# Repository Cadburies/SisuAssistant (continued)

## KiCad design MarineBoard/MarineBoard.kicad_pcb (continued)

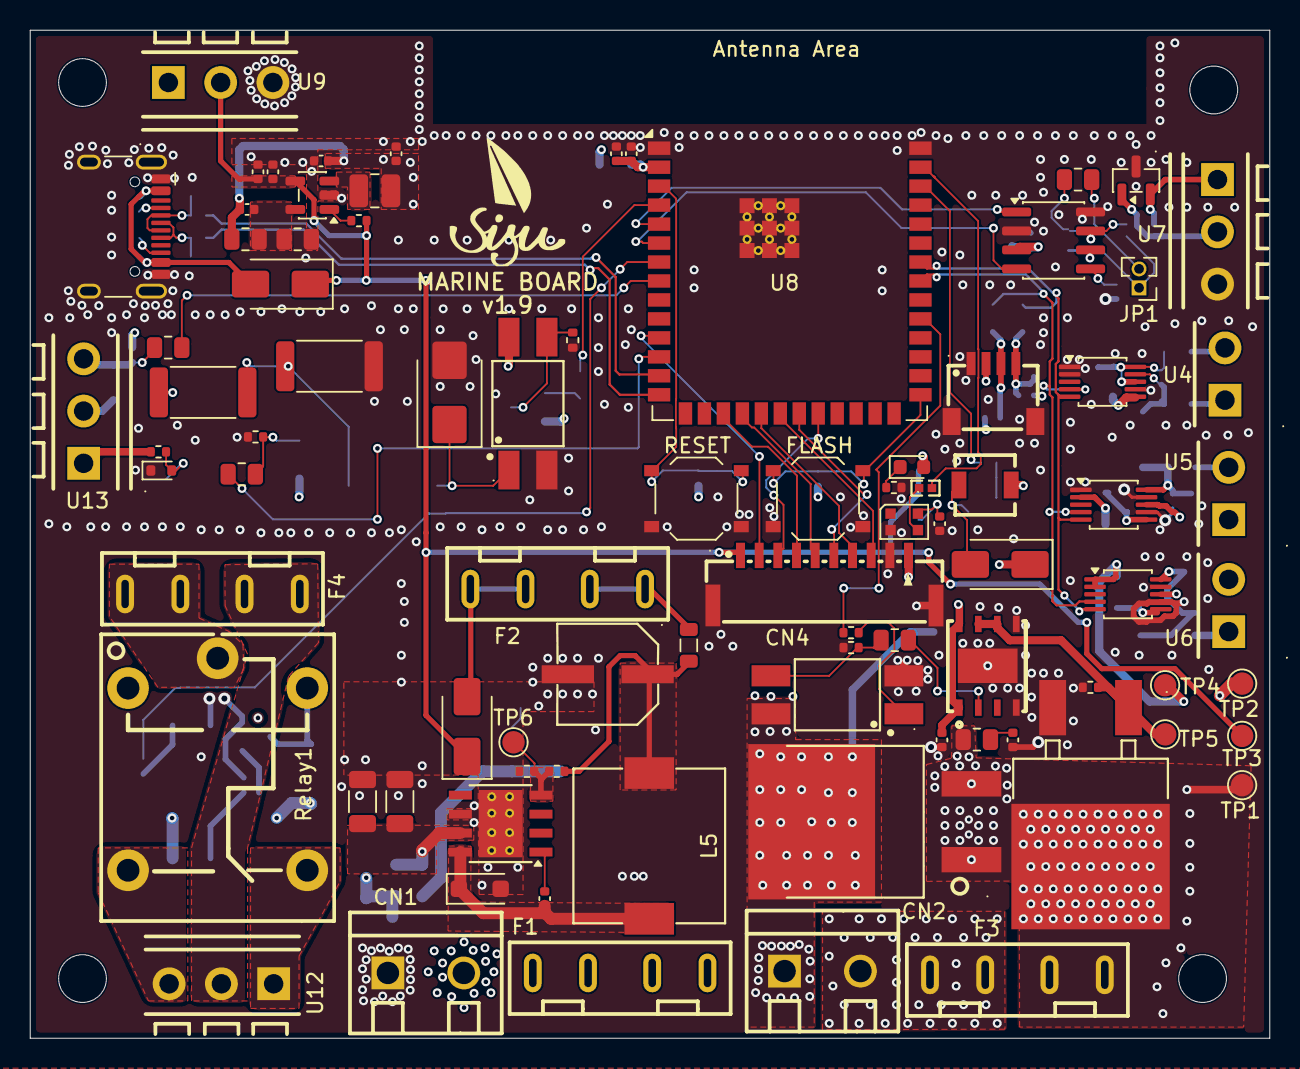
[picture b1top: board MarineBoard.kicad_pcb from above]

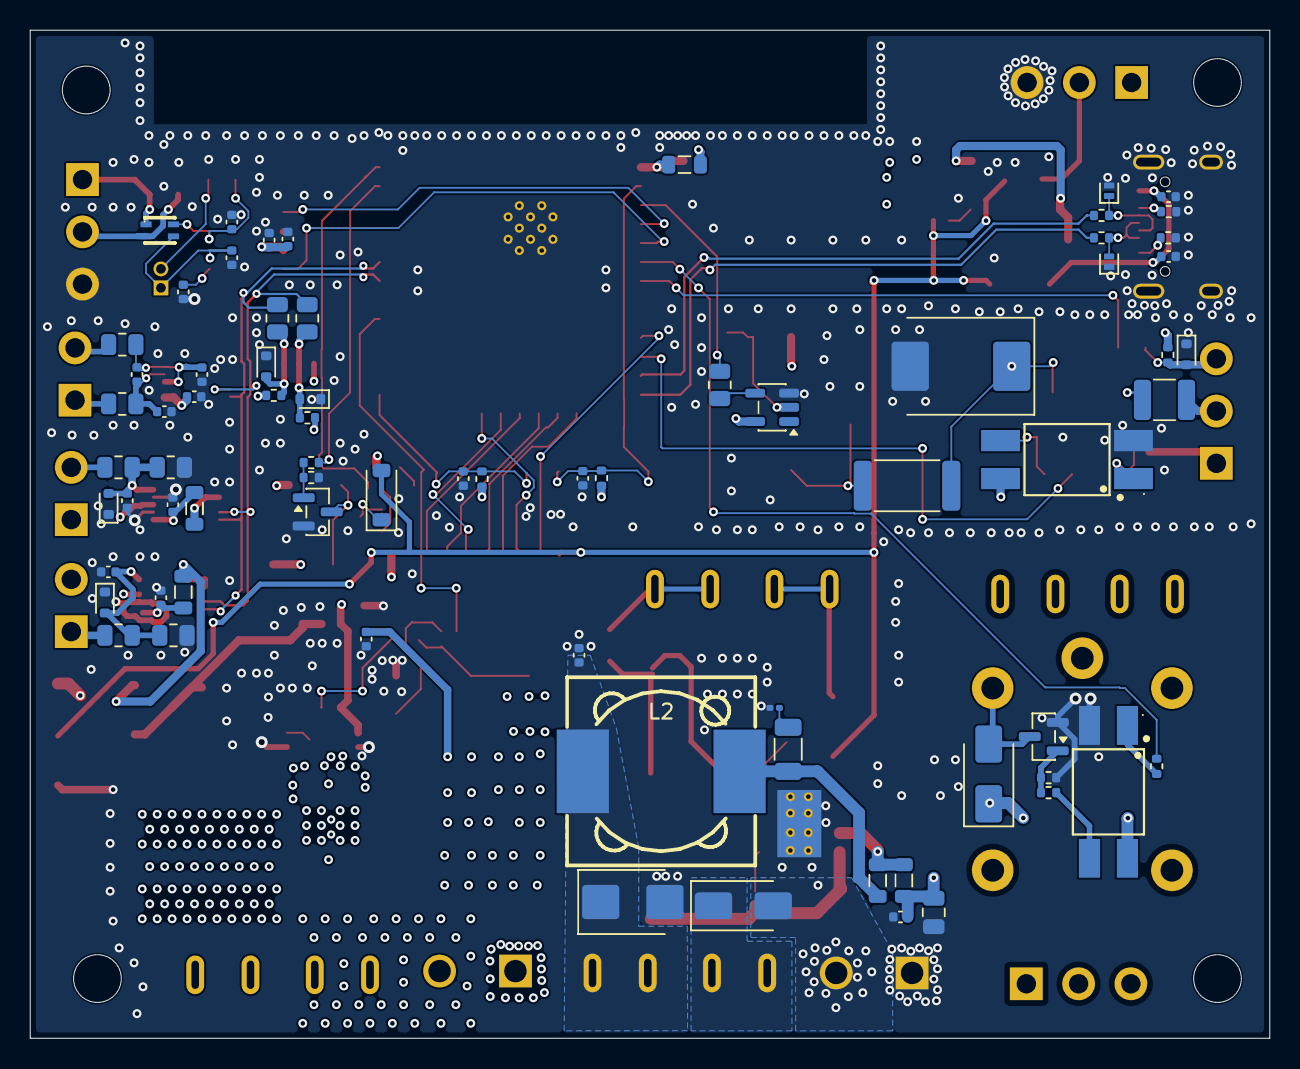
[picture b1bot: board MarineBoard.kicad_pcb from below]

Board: 4 copper layers, 83.0 x 67.5 mm, 162 parts (72 on the bottom side), 95 nets.

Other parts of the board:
LOGO1: v1.9; Sisu_Logo

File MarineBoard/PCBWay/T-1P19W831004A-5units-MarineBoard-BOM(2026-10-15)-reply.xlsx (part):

PCBWay Bom Quotation, Product No.:T-1P19W831004A
Item # | *Designator | *Qty | Manufacturer | *Mfg Part # | Description / Value | *Package/Footprint | Mounting Type | Your Instructions / Notes | Assembly requirement | *Unit Price(5 units) | *Total | *Delivery Time | *Actual Purchase Mfg Part # | *PCBWay Note | Customer Reply | PCBWay Update
1 | BUZZER1 | 1 | KELIKING | KLJ-4020 | 2V~4V 100mA 4kHz 73dB SMD,4x4mm『 』KLJ-4020 | BUZ-SMD_L4.0-W4.0-P3.50-L | SMD |  | Top | 2.174 | 10.87
2 | C1,C25 | 2 | Samsung Electro-Mechanics | CL05A106MQ5NUNC | 10uF ±20% 6.3V Ceramic Capacitor X5R 0402『 』10uF | C_0402_1005Metric | SMD |  | Bottom/Top | 0.099 | 0.99
3 | C2,C3,C5,C7,C9,C24,C27,C28,C31,C32,C34,C35,C36,C37,C38,C40 | 16 | Samsung Electro-Mechanics | CL05B104KO5NNNC | 100nF +/-10% 16V Ceramic Capacitor X7R 0402『 』0.1uF | C_0402_1005Metric | SMD |  | Bottom/Top | 0.008999999999999999 | 0.72
4 | C4,C8 | 2 | muRata | GRM158R61A226ME15D | 22uF +/-20% 10V Ceramic Capacitor X5R 0402『 』22uF | C_0402_1005Metric | SMD |  | Top | 1.029 | 10.29
5 | C6 | 1 | muRata | GJM1555C1H6R8BB01D | 6.8pF 50V Ceramic Capacitor C0G 0402『 』6.8pF | C_0402_1005Metric | SMD |  | Top | 0.266 | 1.33
6 | C11,C12,C14,C19,C42 | 5 | Samsung Electro-Mechanics | CL05B104KB5NNNC | 100nF ±10% 50V Ceramic Capacitor X7R 0402『 』0.1uF | C_0402_1005Metric | SMD |  | Bottom | 0.026 | 0.65
7 | C13 | 1 | muRata | GRM21BR61H106KE43L | 10uF ±10% 50V Ceramic Capacitor X5R 0805『 』10uF/50V | C_0805_2012Metric | SMD |  | Bottom | 0.8 | 4
8 | C15 | 1 | muRata | GRM31CR61E476ME44L | 47uF ±20% 25V Ceramic Capacitor X5R 1206『 』47uF | C_1206_3216Metric | SMD |  | Bottom | 1.959 | 9.795
9 | C16 | 1 | Samsung Electro-Mechanics | CL31B475KBHNNNE | 4.7uF +/-10% 50V Ceramic Capacitor X7R 1206『 』4.7uF | C_1206_3216Metric | SMD |  | Top | 0.485 | 2.425
10 | C17 | 1 | Samsung Electro-Mechanics | CL31A106KBHNNNE | 10uF +/-10% 50V Ceramic Capacitor X5R 1206『 』10uF | C_1206_3216Metric | SMD |  | Top | 1.029 | 5.145
11 | C18 | 1 | Samsung Electro-Mechanics | CL05B103KB5NNNC | 10nF ±10% 50V Ceramic Capacitor X7R 0402『 』10nF | C_0402_1005Metric | SMD |  | Top | 0.126 | 0.63
12 | C20 | 1 | Panasonic | 10SVPE220M | 220uF ±20% 10V OS-CON polymer, ESR 20mΩ, SMD D6.3xL5.9mm (TPS5430 internal comp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 | CAP-SMD_BD6.3-L6.6-W6.6-FD | SMD |  | Top | 3.893 | 19.465
13 | C26,C29 | 2 | muRata | GCM155R71H473KE02D | 47nF ±10% 50V Ceramic Capacitor X7R 0402『 』47nF | C_0402_1005Metric | SMD |  | Bottom | 0.064 | 0.64
14 | C30 | 1 | Samsung Electro-Mechanics | CL05A475MP5NRNC | 4.7uF ±20% 10V Ceramic Capacitor X5R 0402『 』4.7uF | C_0402_1005Metric | SMD |  | Bottom | 0.107 | 0.535
15 | C33 | 1 | muRata | GRM155R61H105KE05D | 1uF ±10% 50V Ceramic Capacitor X5R 0402『 』1uF | C_0402_1005Metric | SMD |  | Top | 0.219 | 1.095
16 | C39 | 1 | PSA | FS32X125K101EGG | 1.2uF +/-10% 100V Ceramic Capacitor X7R 1210『 』1.2uF 100V | C_1210_3225Metric | SMD |  | Bottom | 1.01 | 5.05
17 | CN1,CN2 | 2 | Phoenix Contact | 1729128 | 1.5 17.5A 400V 1x2P Green 16~26 Through Hole 2 1 5.08mm Through Hole,P=5.08mm W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 | CONN-TH_2P-P5.08_1729128 | THT |  | Top | 0.509 | 5.09
18 | CN3 | 1 | JST | SM04B-SRSS-TB(LF)(SN) | Connector Header 4 position 1mm Pitch 1A Surface Mount, Right Angle -25℃~+85℃『 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 | CONN-SMD_4P-P1.00_SM04B-SRSS-TB-LF-SN | SMD |  | Top | 0.712 | 3.56
19 | CN4 | 1 | JST | BM10B-GHS-TBT(LF)(SN) | BM10B-GHS-TBT | CONN-SMD_BM10B-GHS-TBT-LF-SN | SMD |  | Top | 1.57 | 7.850000000000001
20 | D1,D4,D15,D17 | 4 | onsemi | SS14 | 40V 1A Schottky diode, SMA (DO-214AC)『 』SS14 | D_SMA | SMD |  | Bottom/Top | 0.25 | 5
21 | D2,D3 | 2 | R+O | H5VL10B | 5V bidirectional ESD diode H5VL10B. Manufacturer package DFN1006-2L. Board land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 | DFN1006-2L | SMD |  | Bottom | 0.041 | 0.41 |  |  | The correct package for the listed Part Number [H5VL10B] is indeed [DFN1006-2L]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 | Yes. Fit H5VL10B. The manufacturer package is DFN1006-2L. D_SOD-882 is the same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
22 | D5 | 1 | Worldsemi | WS2812B-2020-V6 | RGB LED with integrated controller, Worldsemi WS2812B-2020-V6, 2.0 x 2.0 mm | LED_WS2812B-2020_PLCC4_2.0x2.0mm | SMD |  | Top | 0.062 | 0.31 |  | WS2812B-2020-V6 | The part we supply is WS2812B-2020-V6 OK? | Yes. Fit Worldsemi WS2812B-2020-V6.
23 | D6 | 1 | Littelfuse | SMBJ18A | 18V TVS diode, SMB (DO-214AA)『 』SMBJ18A | D_SMB | SMD |  | Bottom | 0.993 | 4.965 | 7-10 Workdays
24 | D7 | 1 | LRC | LMBR340FT1G | Schottky diode, SOD-123F『 』LMBR340FT1G | D_SOD-123F | SMD |  | Top | 0.169 | 0.8450000000000001
25 | D8 | 1 | Vishay | VS-43CTQ100S-M3 | Dual Schottky rectifier, D2PAK『 』VS-43CTQ100S-M3 | D2PAK_L10.0-W9.0-P2.54-LS15.0-TL-1 | SMD |  | Top | 3.623 | 18.115
26 | D9,D11,D12,D13,D18,D19 | 6 | onsemi | ESD5Z3.3T1G | 3.3V ESD protection diode, SOD-523『 』ESD5Z3.3T1G | D_SOD-523 | SMD |  | Bottom/Top | 0.114 | 3.42
27 | D10 | 1 | UMW | PESD1CAN | CAN bus ESD protection, SOT-23『 』PESD1CAN | SOT-23 | SMD |  | Top | 0.145 | 0.725
28 | D14 | 1 | R+O | SS56 | 60V 5A Schottky diode, SMA『 』SS56 | D_SMA | SMD |  | Bottom | 0.081 | 0.405
29 | D16 | 1 | KENTO | KT-0603R | Red LED 0603『 』KT-0603R | LED_0603_1608Metric | SMD |  | Top | 0.07199999999999999 | 0.36
30 | D20 | 1 | onsemi | MBRS3100T3G | Schottky rectifier, SMC『 』MBRS3100T3G | D_SMC | SMD |  | Bottom | 0.483 | 2.415
31 | D21 | 1 | Diodes Incorporated | 1N4148W-7-F | 75V 150mA switching diode, SOD-123, Diodes Inc 1N4148W-7-F | D_SOD-123 | SMD |  | Bottom | 0.338 | 1.69 | 7-10 Workdays |  | The quoted part number is [1N4148W-7-F], not [WS2812B] as specified in descript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 | Fit Diodes Inc 1N4148W-7-F. This position is a switching diode. The old descrip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
32 | D22 | 1 | Diodes Inc | S3MB-13-F | 1000V 3A rectifier, SMB『 』S3MB-13-F | D_SMB | SMD |  | Top | 0.483 | 2.415
33 | F1 | 1 | XFCN | XF-506P | XF-506P MINI blade fuse holder. Insert Eaton Bussmann ATM-2, 2 A 32 V MINI blad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 | FUSE-TH_XF-506P | THT | Insert Eaton Bussmann ATM-2 into this holder | Top | 0.192 | 0.96 |  |  |  | Solder this holder, then insert Eaton Bussmann ATM-2, 2 A 32 V MINI blade, into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
34 | F2 | 1 | XFCN | XF-506P | XF-506P MINI blade fuse holder. Insert Eaton Bussmann ATM-1, 1 A 32 V MINI blad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 | FUSE-TH_XF-506P | THT | Insert Eaton Bussmann ATM-1 into this holder | Top | 0.192 | 0.96 |  |  |  | Solder this holder, then insert Eaton Bussmann ATM-1, 1 A 32 V MINI blade, into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
35 | F3,F4 | 2 | XFCN | XF-506P | XF-506P MINI blade fuse holder. Insert Eaton Bussmann ATM-10, 10 A 32 V MINI bl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 | FUSE-TH_XF-506P | THT | Insert Eaton Bussmann ATM-10 into each holder | Top | 0.144 | 1.44 |  |  |  | Solder these holders, then insert one Eaton Bussmann ATM-10, 10 A 32 V MINI bla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
36 | Flash1 | 1 | XKB | TS-1187A-B-A-B | TS-1187A tactile switch, 2 pin『 』Flash | SW_Push_1P1T_XKB_TS-1187A | SMD |  | Top | 0.07199999999999999 | 0.36
37 | J1 | 1 | HCTL | HC-TYPE-C-16P-01A | USB 2.0-only 16P Type-C receptacle『 』USB_C_Receptacle_USB2.0_16P | USB_C_Receptacle_HCTL_HC-TYPE-C-16P-01A | SMD |  | Top | 0.242 | 1.21
38 | JP1 | 1 | BOOMELE | 1.27-1*2PPin | 1.27 mm 1x2 vertical pin header. Fit BOOMELE shunt MPN 1.27, LCSC C150949, onto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 | PinHeader_1x02_P1.27mm_Vertical | THT | Fit the BOOMELE 1.27 shunt, LCSC C150949, onto these pins | Top | 0.254 | 1.27 |  | 1.27-1*2P针 |  | Fit BOOMELE shunt MPN 1.27, LCSC C150949, onto these pins.
39 | L1 | 1 | muRata | DFE252012F-1R0M=P2 | 1uH 3.3A shielded inductor, 1008『 』1uH 3.3A 40mΩ | L_1008_2520Metric | SMD |  | Top | 0.242 | 1.21
40 | L2 | 1 | FANGCHENG | FC-DR1207-220MT | 22uH +/-20% shielded inductor, 12.5x12.5 mm, Irms 4A, DCR 40 mohm『 』22uH | IND-SMD_L12.5-W12.5_B82477P4XX | SMD |  | Bottom | 0.39 | 1.95 |  | SMDRI129-220MT
41 | L3,L4,L6 | 3 | muRata | BLM21PG121SN1D | 120 ohm at 100 MHz ferrite bead, 0805『 』BLM21PG121SN1D | L_0805_2012Metric | SMD |  | Bottom/Top | 0.107 | 1.605
42 | L5 | 1 | Sumida | CDRH104RNP-150NC | 15uH shielded inductor, 10.2 x 10.0 mm『 』CDRH104RNP-150NC | IND-SMD_L10.2-W10.0 | SMD |  | Top | 0.966 | 4.83
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
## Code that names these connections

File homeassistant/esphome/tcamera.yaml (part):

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# assumed. Checked this exact "T-Camera" repo/product name too
# (Xinyuan-LilyGO/T-Camera) since the owner found it and it looked
# board-matching at a glance -- it's the SAME older/wrong generation as
# the doc above (three independent tells: XCLK=GPIO4 not 38, OLED I2C on
# 21/22 not 7/6, and critically an IP5306 power chip in its source vs the
# AXP2101 actually on this board/visible in the owner's photo). Not used.
#
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    type: std::string
    restore_value: no

# bus_a (GPIO7/6, OLED+AXP2101) DISABLED 2026-08-12: live hardware fault --
# this exact bus reproducibly wedges with "SCL is held LOW on the bus" /
# ESP-IDF bus-recovery failing, triggering a task-watchdog crash-loop that
# tripped ESPHome's built-in safe_mode. Confirmed the hang happens even
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# bus_b dedicated to the camera's own SCCB (register) interface.
i2c:
  - id: bus_b
    sda: GPIO5
    scl: GPIO4
    scan: true

esp32_camera:
  name: "Dinghy Camera"
  external_clock:
    pin: GPIO38
    frequency: 20MHz
  i2c_id: bus_b
  data_pins: [GPIO14, GPIO47, GPIO48, GPIO21, GPIO13, GPIO11, GPIO10, GPIO9]
  vsync_pin: GPIO8
  href_pin: GPIO18
  pixel_clock_pin: GPIO12
  reset_pin: GPIO39
  # No PSRAM (WROOM-1) -- frame_buffer_location: DRAM is the documented
  # workaround (esphome/issues#6996); XGA is the tested-working ceiling,
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          request_headers:
            Content-Type: application/json

# I2S microphone (T-Camera S3 reference: WS=GPIO42, DATA=GPIO41,
# CLK=GPIO40). Untested on this exact unit -- new addition, not yet
# empirically confirmed the way camera/PIR were.
i2s_audio:
  - id: i2s_mic_bus
    i2s_lrclk_pin: GPIO42
    i2s_bclk_pin: GPIO40

microphone:
  - platform: i2s_audio
    id: dinghy_mic
    i2s_audio_id: i2s_mic_bus
    adc_type: external
    i2s_din_pin: GPIO41
    channel: left
    sample_rate: 16000
    bits_per_sample: 16bit
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
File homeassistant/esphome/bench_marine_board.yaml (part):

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# Fallback AP: "MarineBoard-Bench" (password !secret ap_password).
#
# OWON HDS2102S ident (set 50% duty, then measure):
#   GPIO1  LED   default 500 Hz
#   GPIO38 PWM1  default 4000 Hz (same as packages/marine_alternator.yaml)
#   GPIO2  buzzer  PWM (warn/fault demo buttons; not a static GPIO)
#   GPIO7  relay   DC on/off; optional 1 Hz square for coil/opto
# USB-C does not power relay coil, PWM MOSFET, or 4–20 mA loops — CN1 12 V.
# =============================================================================

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      sorting_weight: 90

i2c:
  sda: GPIO40
  scl: GPIO41
  scan: true
  id: i2c_bus
  frequency: 100kHz

one_wire:
  - platform: gpio
    pin: GPIO15
    id: ow_tmp1

globals:
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
output:
  - platform: ledc
    pin: GPIO1
    id: led_out
    frequency: 500 Hz
  - platform: ledc
    pin: GPIO2
    id: buzz_out
    frequency: 4000 Hz
  - platform: gpio
    pin: GPIO7
    id: rly_out
    inverted: false
  - platform: ledc
    pin: GPIO38
    id: pwm1_out
    frequency: 4000 Hz

switch:
  - platform: template
    name: "LED GPIO1"
    id: led_sw
    restore_mode: ALWAYS_OFF
    optimistic: true
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          id: led_out
          level: 0.0
  - platform: template
    name: "Buzzer GPIO2"
    id: buzz_sw
    restore_mode: ALWAYS_OFF
    optimistic: true
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          id: buzz_out
          level: 0.0
  - platform: output
    name: "Relay GPIO7"
    id: rly_sw
    output: rly_out
    restore_mode: ALWAYS_OFF
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      sorting_group_id: grp_outputs
      sorting_weight: 30
  - platform: template
    name: "LED 2 Hz blink (GPIO1)"
    id: led_blink_sw
    restore_mode: ALWAYS_OFF
    optimistic: true
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          id: led_out
          level: 0.0
  - platform: template
    name: "Relay 1 Hz square (GPIO7)"
    id: rly_1hz_sw
    restore_mode: ALWAYS_OFF
    optimistic: true
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
number:
  - platform: template
    name: "LED duty % (GPIO1)"
    id: led_duty
    min_value: 0
    max_value: 100
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          id: led_out
          level: !lambda "return x / 100.0f;"
  - platform: template
    name: "LED freq Hz (GPIO1)"
    id: led_hz
    min_value: 1
    max_value: 5000
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          id: led_out
          frequency: !lambda "return x;"
  - platform: template
    name: "Buzzer tone Hz (GPIO2)"
    id: buzz_hz
    min_value: 500
    max_value: 8000
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          id: buzz_out
          frequency: !lambda "return x;"
  - platform: template
    name: "PWM1 duty % (GPIO38)"
    id: pwm1_duty
    min_value: 0
    max_value: 100
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          id: pwm1_out
          level: !lambda "return x / 100.0f;"
  - platform: template
    name: "PWM1 freq Hz (GPIO38)"
    id: pwm1_hz
    min_value: 50
    max_value: 20000
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binary_sensor:
  - platform: gpio
    pin:
      number: GPIO8
      mode:
        input: true
    name: "ENBL GPIO8"
    id: enbl_in
    filters:
      - delayed_on: 20ms
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      sorting_weight: 10
  - platform: gpio
    pin:
      number: GPIO4
      allow_other_uses: true
      mode:
        input: true
    name: "RPM GPIO4 level"
    id: rpm_level
    web_server:
      sorting_group_id: grp_inputs
      sorting_weight: 20
  - platform: gpio
    pin:
      number: GPIO6
      mode:
        input: true
    name: "CAN RX GPIO6 (listen only)"
    id: can_rx
    web_server:
      sorting_group_id: grp_inputs
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sensor:
  - platform: pulse_counter
    pin:
      number: GPIO4
      allow_other_uses: true
      mode:
        input: true
    name: "RPM GPIO4 pulses per min"
    id: rpm_count
    unit_of_measurement: "pulses/min"
    update_interval: 2s
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      sorting_weight: 21
  - platform: dallas_temp
    one_wire_id: ow_tmp1
    name: "TMP1 DS18B20 GPIO15"
    id: tmp1
    unit_of_measurement: "°C"
    accuracy_decimals: 1
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      sorting_group_id: grp_scope
      sorting_weight: 90
    lambda: |-
      return {"LED=GPIO1  BUZZ=GPIO2 (PWM helpers)  RPM=GPIO4  RLY=GPIO7  ENBL=GPIO8  TMP1=GPIO15  PWM1=GPIO38  SDA=40 SCL=41  CAN TX=5 RX=6"};

interval:
  - interval: 250ms
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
